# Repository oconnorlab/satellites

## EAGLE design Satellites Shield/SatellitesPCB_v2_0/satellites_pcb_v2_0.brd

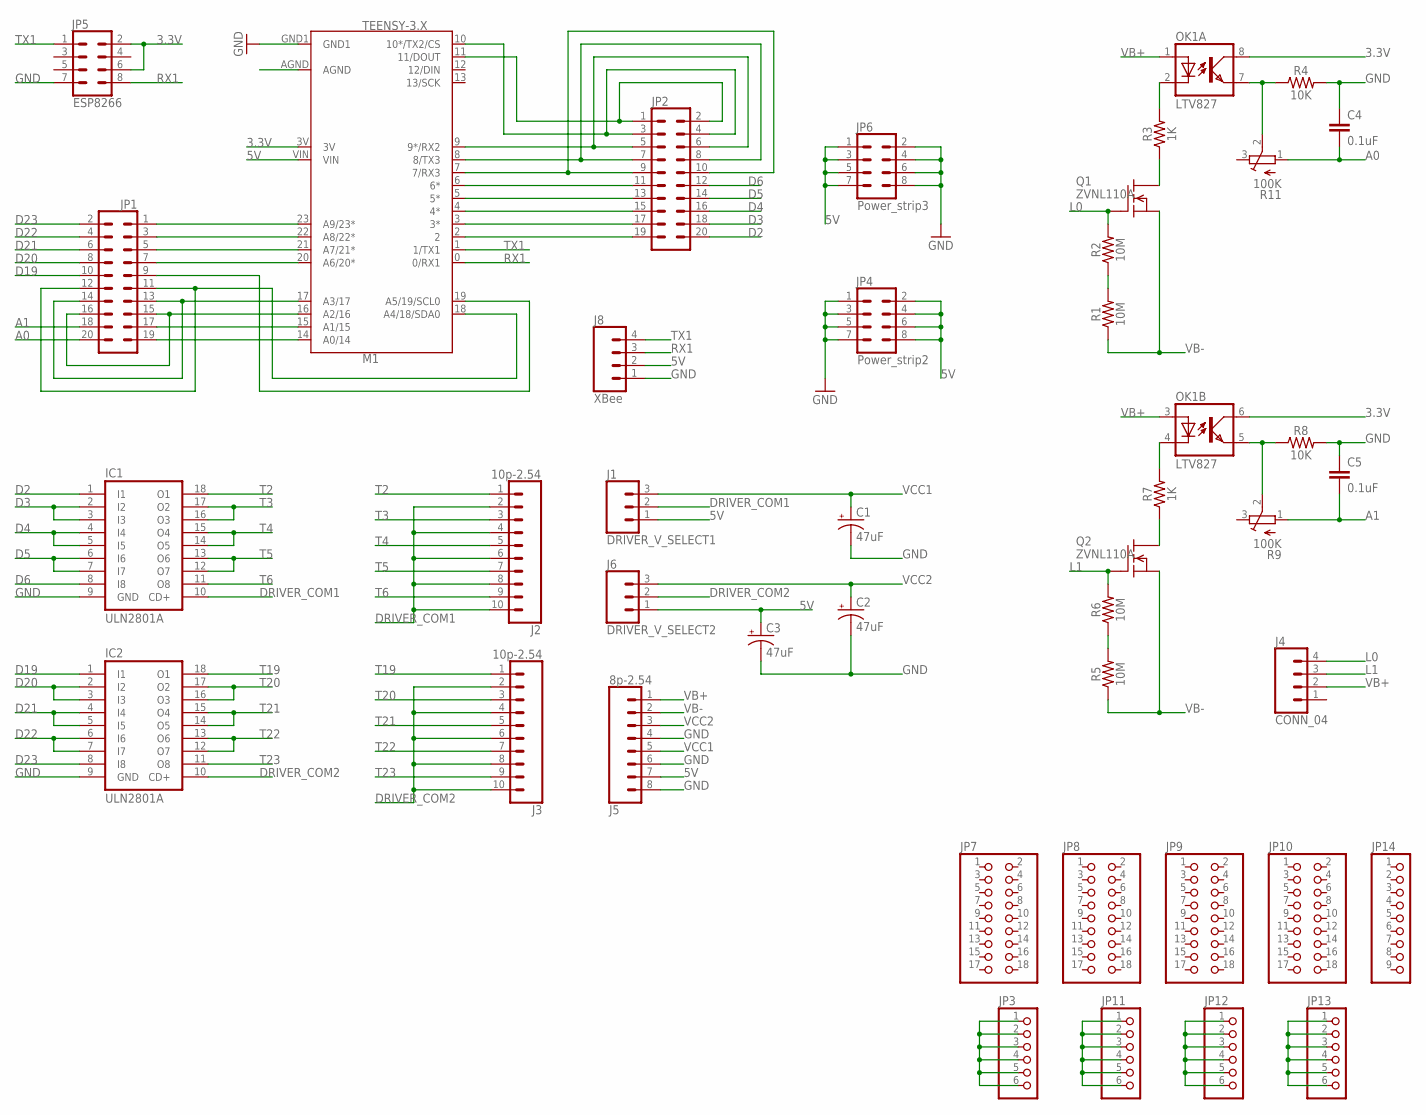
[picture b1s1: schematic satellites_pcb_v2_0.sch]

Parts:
C1, C2, C3: 47uF; CPOL-RADIAL-2.5MM-6.5MM
C4, C5: 0.1uF; CAP-PTH-2.54
IC1, IC2: ULN2801A; DIL18
J1: DRIVER_V_SELECT1; 1X03_LOCK
J2, J3: 10p-2.54; SCREW_TERMINAL_10P_2.54MM_LONGPAD
J4: CONN_04; SCREW_TERMINAL_4P_2.54MM
J5: 8p-2.54; SCREW_TERMINAL_8P_2.54MM_LONGPAD
J6: DRIVER_V_SELECT2; 1X03_LOCK
J8: XBee; 1X04_LOCK
JP1, JP2: CONN_10X2; 2X10
JP3, JP11, JP12, JP13: PINHD-1X6CLEAN; 1X06-CLEAN
JP4: Power_strip2; 2X4
JP5: ESP8266; 2X4
JP6: Power_strip3; 2X4
JP7, JP8, JP9, JP10: PINHD-2X9-CBIG; 2X09-CLEANBIG
JP14: PINHD-1X9; 1X09-BIG
M1: TEENSY-3.X; TEENSY-3.1_NOSILK
OK1: LTV827; DIP08
Q1, Q2: ZVNL110A; TO92
R1, R2, R5, R6: 10M; AXIAL-0.3
R3, R7: 1K; AXIAL-0.3
R4, R8: 10K; AXIAL-0.3
R9, R11: 100K; TRIM-3386H

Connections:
3.3V: JP5.2, JP5.6, M1.3V, OK1.6 (COL), OK1.8 (COL)
5V: C3.1 (+), J1.1, J5.7, J6.1, J8.2, JP4.2, JP4.4, JP4.6, JP4.8, JP6.1, JP6.3, JP6.5, JP6.7, M1.VIN
A0: C4.2, JP1.20, R11.1 (A)
A1: C5.2, JP1.18, R9.1 (A)
D2: IC1.1 (I1), JP2.20
D3: IC1.2 (I2), IC1.3 (I3), JP2.18
D4: IC1.4 (I4), IC1.5 (I5), JP2.16
D5: IC1.6 (I6), IC1.7 (I7), JP2.14
D6: IC1.8 (I8), JP2.12
D19: IC2.1 (I1), JP1.10
D20: IC2.2 (I2), IC2.3 (I3), JP1.8
D21: IC2.4 (I4), IC2.5 (I5), JP1.6
D22: IC2.6 (I6), IC2.7 (I7), JP1.4
D23: IC2.8 (I8), JP1.2
DRIVER_COM1: IC1.10 (CD+), J1.2, J2.2, J2.4, J2.6, J2.8, J2.10
DRIVER_COM2: IC2.10 (CD+), J3.2, J3.4, J3.6, J3.8, J3.10, J6.2
GND: C1.2 (-), C2.2 (-), C3.2 (-), C4.1, C5.1, IC1.9 (GND), IC2.9 (GND), J5.4, J5.6, J5.8, J8.1, JP4.1, JP4.3, JP4.5, JP4.7, JP5.7, JP6.2, JP6.4, JP6.6, JP6.8, M1.GND1, R4.P$2 (2), R8.P$2 (2)
L0: J4.4, Q1.2 (G), R2.P$2 (2)
L1: J4.3, Q2.2 (G), R6.P$2 (2)
unnamed: JP1.1, M1.23 (A9/23*)
unnamed: JP1.3, M1.22 (A8/22*)
unnamed: JP2.5, JP2.6, M1.9 (9*/RX2)
unnamed: JP2.7, JP2.8, M1.8 (8/TX3)
unnamed: OK1.7 (EMIT), R4.P$1 (1), R11.2 (S)
unnamed: JP2.11, M1.6 (6*)
unnamed: JP2.13, M1.5 (5*)
unnamed: JP2.3, JP2.4, M1.10 (10*/TX2/CS)
unnamed: JP2.15, M1.4 (4*)
unnamed: JP1.5, M1.21 (A7/21*)
unnamed: JP1.7, M1.20 (A6/20*)
unnamed: OK1.5 (EMIT), R8.P$1 (1), R9.2 (S)
unnamed: Q1.1 (D), R3.P$1 (1)
unnamed: JP2.17, M1.3 (3*)
unnamed: R1.P$2 (2), R2.P$1 (1)
unnamed: JP2.19, M1.2
unnamed: JP1.15, JP1.16, M1.16 (A2/16)
unnamed: JP1.17, M1.15 (A1/15)
unnamed: JP1.19, M1.14 (A0/14)
unnamed: JP1.11, JP1.12, M1.18 (A4/18/SDA0)
unnamed: JP1.9, M1.19 (A5/19/SCL0)
unnamed: OK1.2 (C), R3.P$2 (2)
unnamed: R5.P$2 (2), R6.P$1 (1)
unnamed: Q2.1 (D), R7.P$1 (1)
unnamed: OK1.4 (C), R7.P$2 (2)
unnamed: JP3.1, JP3.2, JP3.3, JP3.4, JP3.5, JP3.6
unnamed: JP11.1, JP11.2, JP11.3, JP11.4, JP11.5, JP11.6
unnamed: JP12.1, JP12.2, JP12.3, JP12.4, JP12.5, JP12.6
unnamed: JP2.9, JP2.10, M1.7 (7/RX3)
unnamed: JP13.1, JP13.2, JP13.3, JP13.4, JP13.5, JP13.6
unnamed: JP1.13, JP1.14, M1.17 (A3/17)
unnamed: JP2.1, JP2.2, M1.11 (11/DOUT)
RX1: J8.3, JP5.8, M1.0 (0/RX1)
T2: IC1.18 (O1), J2.1
T3: IC1.16 (O3), IC1.17 (O2), J2.3
T4: IC1.14 (O5), IC1.15 (O4), J2.5
T5: IC1.12 (O7), IC1.13 (O6), J2.7
T6: IC1.11 (O8), J2.9
T19: IC2.18 (O1), J3.1
T20: IC2.16 (O3), IC2.17 (O2), J3.3
T21: IC2.14 (O5), IC2.15 (O4), J3.5
T22: IC2.12 (O7), IC2.13 (O6), J3.7
T23: IC2.11 (O8), J3.9
TX1: J8.4, JP5.1, M1.1 (1/TX1)
VB+: J4.2, J5.1, OK1.1 (A), OK1.3 (A)
VB-: J5.2, Q1.3 (S), Q2.3 (S), R1.P$1 (1), R5.P$1 (1)
VCC1: C1.1 (+), J1.3, J5.5
VCC2: C2.1 (+), J5.3, J6.3

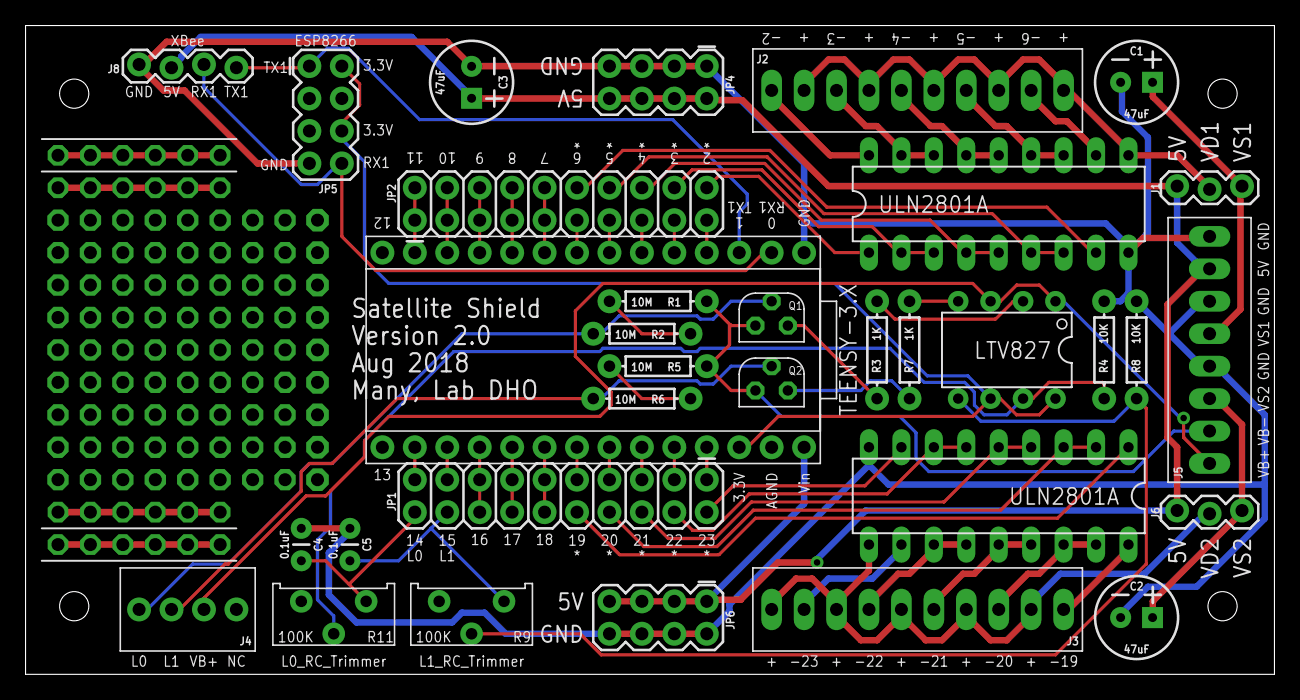
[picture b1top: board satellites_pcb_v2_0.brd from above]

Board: 2 copper layers, 97.8 x 50.8 mm, 42 parts (0 on the bottom side), 67 nets.

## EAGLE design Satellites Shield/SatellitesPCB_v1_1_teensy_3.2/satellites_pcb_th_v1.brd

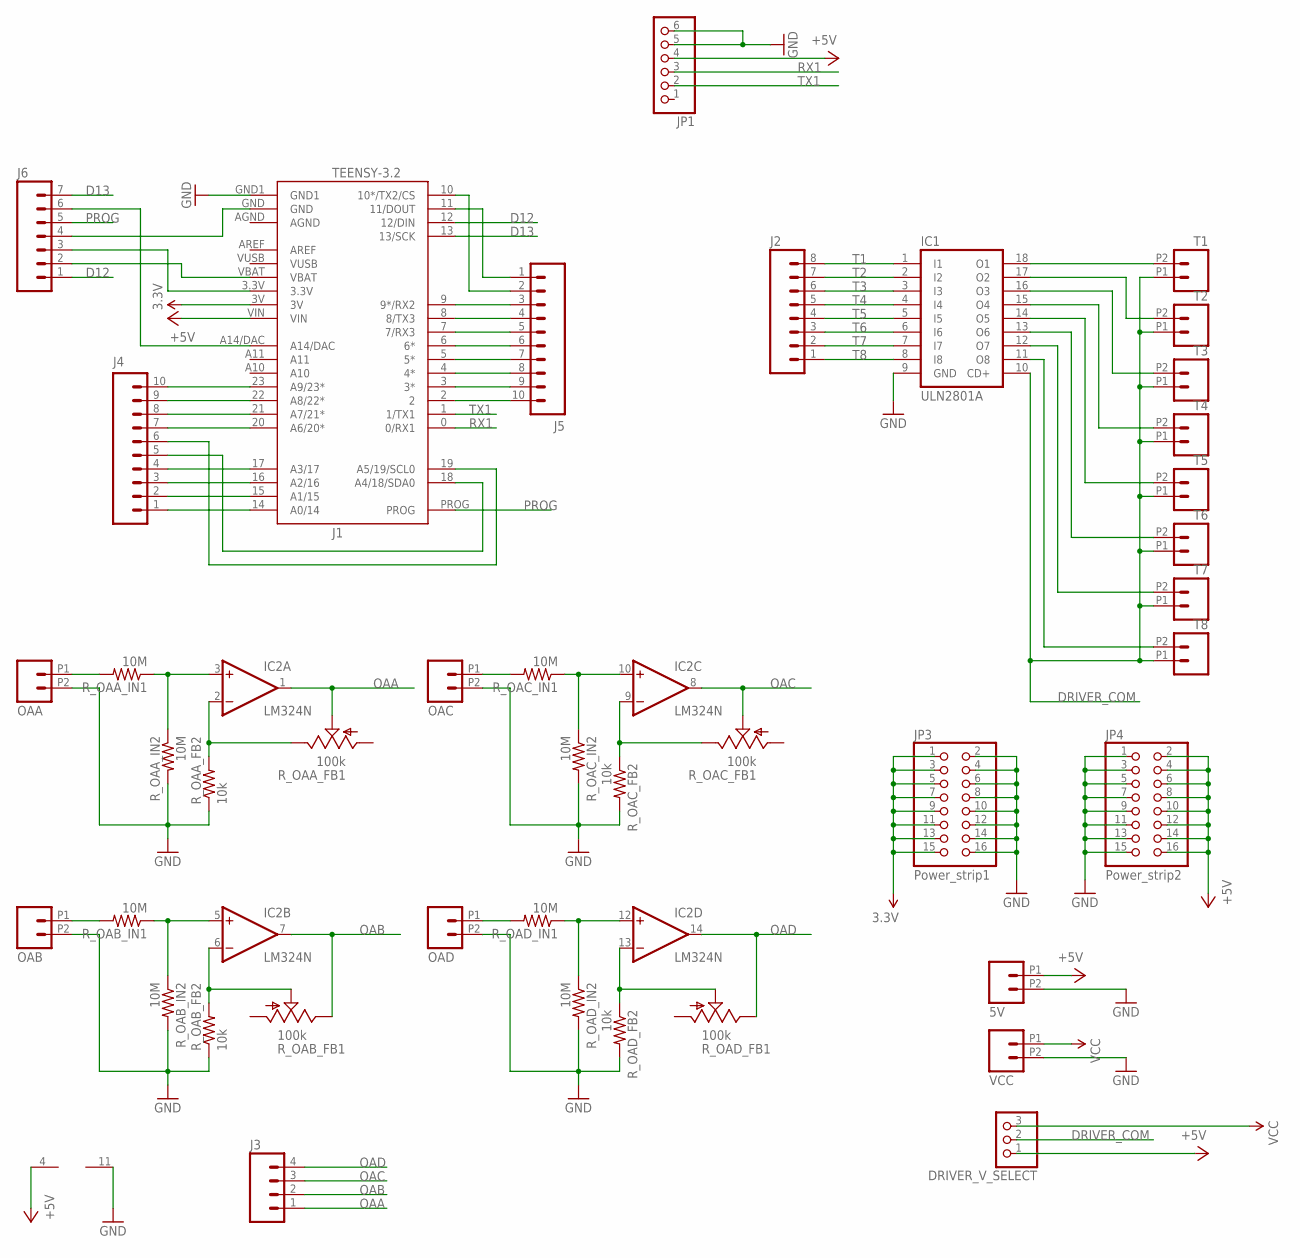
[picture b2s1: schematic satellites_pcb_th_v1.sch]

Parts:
5V: M022.54MM_SCREWTERM; 1X02_2.54_SCREWTERM
DRIVER_V_SELECT: PINHD-1X3; 1X03
IC1: ULN2801A; DIL18
IC2: LM324N; DIL14
J1: TEENSY-3.2; TEENSY-3.1_NOSILK
J2: M08; 1X08_ROUND
J3: M04PTH; 1X04
J4, J5: M10NO_SILK_PTH_FEMALE; 1X10_NO_SILK
J6: M07; 1X07
JP1: PINHD-1X6; 1X06
JP3: Power_strip1; 2X08
JP4: Power_strip2; 2X08
OAA: M022.54MM_SCREWTERM; 1X02_2.54_SCREWTERM
OAB: M022.54MM_SCREWTERM; 1X02_2.54_SCREWTERM
OAC: M022.54MM_SCREWTERM; 1X02_2.54_SCREWTERM
OAD: M022.54MM_SCREWTERM; 1X02_2.54_SCREWTERM
R_OAA_FB1: 100k; B64W
R_OAA_FB2: 10k; AXIAL-0.3
R_OAA_IN1, R_OAA_IN2: 10M; AXIAL-0.3
R_OAB_FB1: 100k; B64W
R_OAB_FB2: 10k; AXIAL-0.3
R_OAB_IN1, R_OAB_IN2: 10M; AXIAL-0.3
R_OAC_FB1: 100k; B64W
R_OAC_FB2: 10k; AXIAL-0.3
R_OAC_IN1, R_OAC_IN2: 10M; AXIAL-0.3
R_OAD_FB1: 100k; B64W
R_OAD_FB2: 10k; AXIAL-0.3
R_OAD_IN1, R_OAD_IN2: 10M; AXIAL-0.3
T1, T2, T3, T4, T5, T6, T7, T8: M022.54MM_SCREWTERM; 1X02_2.54_SCREWTERM
VCC: M022.54MM_SCREWTERM; 1X02_2.54_SCREWTERM

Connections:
3.3V: J1.3V, JP3.1, JP3.3, JP3.5, JP3.7, JP3.9, JP3.11, JP3.13, JP3.15
+5V: 5V.P1 (1), DRIVER_V_SELECT.1, IC2.4 (V+), J1.VIN, JP1.4, JP4.2, JP4.4, JP4.6, JP4.8, JP4.10, JP4.12, JP4.14, JP4.16
D12: J1.12 (12/DIN), J6.1
D13: J1.13 (13/SCK), J6.7
DRIVER_COM: DRIVER_V_SELECT.2, IC1.10 (CD+), T1.P1 (1), T2.P1 (1), T3.P1 (1), T4.P1 (1), T5.P1 (1), T6.P1 (1), T7.P1 (1), T8.P1 (1)
GND: 5V.P2 (2), IC1.9 (GND), IC2.11 (V-), J1.GND1, JP1.5, JP1.6, JP3.2, JP3.4, JP3.6, JP3.8, JP3.10, JP3.12, JP3.14, JP3.16, JP4.1, JP4.3, JP4.5, JP4.7, JP4.9, JP4.11, JP4.13, JP4.15, OAA.P2 (2), OAB.P2 (2), OAC.P2 (2), OAD.P2 (2), R_OAA_FB2.P$1 (1), R_OAA_IN2.P$2 (2), R_OAB_FB2.P$1 (1), R_OAB_IN2.P$2 (2), R_OAC_FB2.P$2 (2), R_OAC_IN2.P$2 (2), R_OAD_FB2.P$2 (2), R_OAD_IN2.P$2 (2), VCC.P2 (2)
unnamed: J1.14 (A0/14), J4.1
unnamed: J1.23 (A9/23*), J4.10
unnamed: J1.9 (9*/RX2), J5.3
unnamed: J1.8 (8/TX3), J5.4
unnamed: J1.7 (7/RX3), J5.5
unnamed: J1.6 (6*), J5.6
unnamed: J1.5 (5*), J5.7
unnamed: J1.10 (10*/TX2/CS), J5.2
unnamed: OAB.P1 (1), R_OAB_IN1.P$2 (2)
unnamed: J1.22 (A8/22*), J4.9
unnamed: J1.21 (A7/21*), J4.8
unnamed: J1.20 (A6/20*), J4.7
unnamed: IC2.3 (+IN), R_OAA_IN1.P$1 (1), R_OAA_IN2.P$1 (1)
unnamed: OAC.P1 (1), R_OAC_IN1.P$2 (2)
unnamed: IC2.10 (+IN), R_OAC_IN1.P$1 (1), R_OAC_IN2.P$1 (1)
unnamed: OAD.P1 (1), R_OAD_IN1.P$2 (2)
unnamed: J1.17 (A3/17), J4.4
unnamed: J1.16 (A2/16), J4.3
unnamed: J1.15 (A1/15), J4.2
unnamed: J1.18 (A4/18/SDA0), J4.5
unnamed: J1.19 (A5/19/SCL0), J4.6
unnamed: IC1.11 (O8), T8.P2 (2)
unnamed: J1.4 (4*), J5.8
unnamed: J1.3 (3*), J5.9
unnamed: IC1.18 (O1), T1.P2 (2)
unnamed: IC1.17 (O2), T2.P2 (2)
unnamed: IC1.16 (O3), T3.P2 (2)
unnamed: IC1.15 (O4), T4.P2 (2)
unnamed: IC1.14 (O5), T5.P2 (2)
unnamed: IC1.13 (O6), T6.P2 (2)
unnamed: IC1.12 (O7), T7.P2 (2)
unnamed: J1.2, J5.10
unnamed: J1.11 (11/DOUT), J5.1
unnamed: J1.VBAT, J6.2
unnamed: J1.A14/DAC, J6.6
unnamed: IC2.2 (-IN), R_OAA_FB1.E, R_OAA_FB2.P$2 (2)
unnamed: IC2.6 (-IN), R_OAB_FB1.S, R_OAB_FB2.P$2 (2)
unnamed: IC2.9 (-IN), R_OAC_FB1.E, R_OAC_FB2.P$1 (1)
unnamed: J1.3.3V, J6.3
unnamed: IC2.13 (-IN), R_OAD_FB1.S, R_OAD_FB2.P$1 (1)
unnamed: J1.GND, J6.4
unnamed: OAA.P1 (1), R_OAA_IN1.P$2 (2)
unnamed: IC2.5 (+IN), R_OAB_IN1.P$1 (1), R_OAB_IN2.P$1 (1)
unnamed: IC2.12 (+IN), R_OAD_IN1.P$1 (1), R_OAD_IN2.P$1 (1)
OAA: IC2.1 (OUT), J3.1, R_OAA_FB1.S
OAB: IC2.7 (OUT), J3.2, R_OAB_FB1.E
OAC: IC2.8 (OUT), J3.3, R_OAC_FB1.S
OAD: IC2.14 (OUT), J3.4, R_OAD_FB1.E
PROG: J1.PROG, J6.5
RX1: J1.0 (0/RX1), JP1.3
T1: IC1.1 (I1), J2.8
T2: IC1.2 (I2), J2.7
T3: IC1.3 (I3), J2.6
T4: IC1.4 (I4), J2.5
T5: IC1.5 (I5), J2.4
T6: IC1.6 (I6), J2.3
T7: IC1.7 (I7), J2.2
T8: IC1.8 (I8), J2.1
TX1: J1.1 (1/TX1), JP1.2
VCC: DRIVER_V_SELECT.3, VCC.P1 (1)

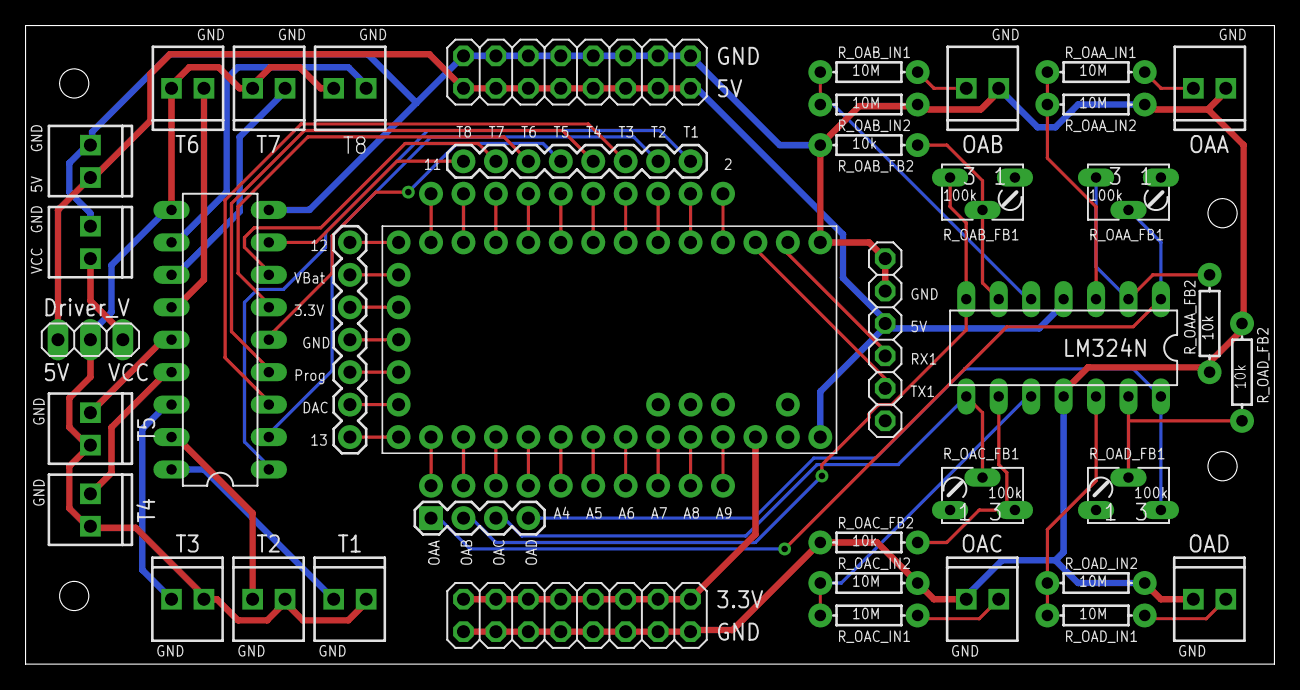
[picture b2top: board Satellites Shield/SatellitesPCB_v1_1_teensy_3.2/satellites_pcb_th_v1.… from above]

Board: 2 copper layers, 97.8 x 50.0 mm, 42 parts (0 on the bottom side), 66 nets.

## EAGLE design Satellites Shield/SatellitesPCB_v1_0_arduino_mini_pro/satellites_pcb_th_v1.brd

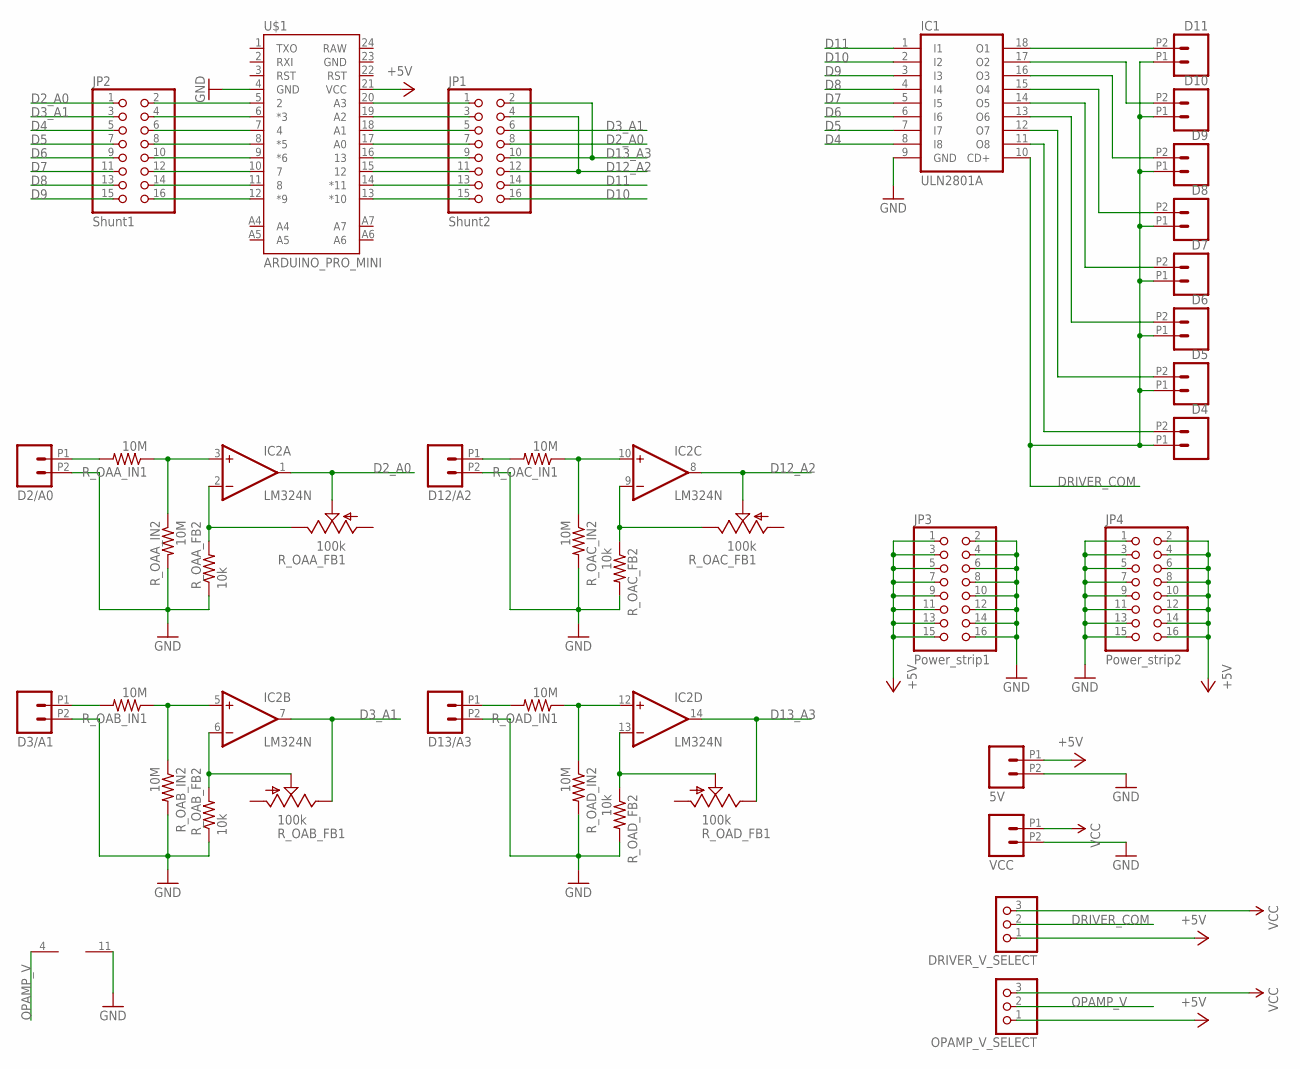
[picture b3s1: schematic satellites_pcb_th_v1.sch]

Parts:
5V: M022.54MM_SCREWTERM; 1X02_2.54_SCREWTERM
D2/A0, D3/A1, D4, D5, D6, D7, D8, D9, D10, D11, D12/A2, D13/A3: M022.54MM_SCREWTERM; 1X02_2.54_SCREWTERM
DRIVER_V_SELECT: PINHD-1X3; 1X03
IC1: ULN2801A; DIL18
IC2: LM324N; DIL14
JP1: Shunt2; 2X08
JP2: Shunt1; 2X08
JP3: Power_strip1; 2X08
JP4: Power_strip2; 2X08
OPAMP_V_SELECT: PINHD-1X3; 1X03
R_OAA_FB1: 100k; B64W
R_OAA_FB2: 10k; AXIAL-0.3
R_OAA_IN1, R_OAA_IN2: 10M; AXIAL-0.3
R_OAB_FB1: 100k; B64W
R_OAB_FB2: 10k; AXIAL-0.3
R_OAB_IN1, R_OAB_IN2: 10M; AXIAL-0.3
R_OAC_FB1: 100k; B64W
R_OAC_FB2: 10k; AXIAL-0.3
R_OAC_IN1, R_OAC_IN2: 10M; AXIAL-0.3
R_OAD_FB1: 100k; B64W
R_OAD_FB2: 10k; AXIAL-0.3
R_OAD_IN1, R_OAD_IN2: 10M; AXIAL-0.3
U$1: ARDUINO_PRO_MINI
VCC: M022.54MM_SCREWTERM; 1X02_2.54_SCREWTERM

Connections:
+5V: 5V.P1 (1), DRIVER_V_SELECT.1, JP3.1, JP3.3, JP3.5, JP3.7, JP3.9, JP3.11, JP3.13, JP3.15, JP4.2, JP4.4, JP4.6, JP4.8, JP4.10, JP4.12, JP4.14, JP4.16, OPAMP_V_SELECT.1, U$1.21 (VCC)
D2_A0: IC2.1 (OUT), JP1.8, JP2.1, R_OAA_FB1.S
D3_A1: IC2.7 (OUT), JP1.6, JP2.3, R_OAB_FB1.E
D4: IC1.8 (I8), JP2.5
D5: IC1.7 (I7), JP2.7
D6: IC1.6 (I6), JP2.9
D7: IC1.5 (I5), JP2.11
D8: IC1.4 (I4), JP2.13
D9: IC1.3 (I3), JP2.15
D10: IC1.2 (I2), JP1.16
D11: IC1.1 (I1), JP1.14
D12_A2: IC2.8 (OUT), JP1.4, JP1.12, R_OAC_FB1.S
D13_A3: IC2.14 (OUT), JP1.2, JP1.10, R_OAD_FB1.E
DRIVER_COM: D4.P1 (1), D5.P1 (1), D6.P1 (1), D7.P1 (1), D8.P1 (1), D9.P1 (1), D10.P1 (1), D11.P1 (1), DRIVER_V_SELECT.2, IC1.10 (CD+)
GND: 5V.P2 (2), D2/A0.P2 (2), D3/A1.P2 (2), D12/A2.P2 (2), D13/A3.P2 (2), IC1.9 (GND), IC2.11 (V-), JP3.2, JP3.4, JP3.6, JP3.8, JP3.10, JP3.12, JP3.14, JP3.16, JP4.1, JP4.3, JP4.5, JP4.7, JP4.9, JP4.11, JP4.13, JP4.15, R_OAA_FB2.P$1 (1), R_OAA_IN2.P$2 (2), R_OAB_FB2.P$1 (1), R_OAB_IN2.P$2 (2), R_OAC_FB2.P$2 (2), R_OAC_IN2.P$2 (2), R_OAD_FB2.P$2 (2), R_OAD_IN2.P$2 (2), U$1.4 (GND), VCC.P2 (2)
unnamed: JP2.2, U$1.5 (2)
unnamed: JP2.4, U$1.6 (*3)
unnamed: JP2.6, U$1.7 (4)
unnamed: JP2.8, U$1.8 (*5)
unnamed: JP2.10, U$1.9 (*6)
unnamed: JP2.12, U$1.10 (7)
unnamed: JP2.14, U$1.11 (8)
unnamed: JP2.16, U$1.12 (*9)
unnamed: D3/A1.P1 (1), R_OAB_IN1.P$2 (2)
unnamed: JP1.1, U$1.20 (A3)
unnamed: JP1.3, U$1.19 (A2)
unnamed: JP1.5, U$1.18 (A1)
unnamed: IC2.3 (+IN), R_OAA_IN1.P$1 (1), R_OAA_IN2.P$1 (1)
unnamed: D12/A2.P1 (1), R_OAC_IN1.P$2 (2)
unnamed: IC2.10 (+IN), R_OAC_IN1.P$1 (1), R_OAC_IN2.P$1 (1)
unnamed: D13/A3.P1 (1), R_OAD_IN1.P$2 (2)
unnamed: JP1.7, U$1.17 (A0)
unnamed: JP1.9, U$1.16 (13)
unnamed: JP1.11, U$1.15 (12)
unnamed: JP1.13, U$1.14 (*11)
unnamed: JP1.15, U$1.13 (*10)
unnamed: D4.P2 (2), IC1.11 (O8)
unnamed: D11.P2 (2), IC1.18 (O1)
unnamed: D10.P2 (2), IC1.17 (O2)
unnamed: D9.P2 (2), IC1.16 (O3)
unnamed: D8.P2 (2), IC1.15 (O4)
unnamed: D7.P2 (2), IC1.14 (O5)
unnamed: D6.P2 (2), IC1.13 (O6)
unnamed: D5.P2 (2), IC1.12 (O7)
unnamed: IC2.2 (-IN), R_OAA_FB1.E, R_OAA_FB2.P$2 (2)
unnamed: IC2.6 (-IN), R_OAB_FB1.S, R_OAB_FB2.P$2 (2)
unnamed: IC2.9 (-IN), R_OAC_FB1.E, R_OAC_FB2.P$1 (1)
unnamed: IC2.13 (-IN), R_OAD_FB1.S, R_OAD_FB2.P$1 (1)
unnamed: D2/A0.P1 (1), R_OAA_IN1.P$2 (2)
unnamed: IC2.5 (+IN), R_OAB_IN1.P$1 (1), R_OAB_IN2.P$1 (1)
unnamed: IC2.12 (+IN), R_OAD_IN1.P$1 (1), R_OAD_IN2.P$1 (1)
OPAMP_V: IC2.4 (V+), OPAMP_V_SELECT.2
VCC: DRIVER_V_SELECT.3, OPAMP_V_SELECT.3, VCC.P1 (1)

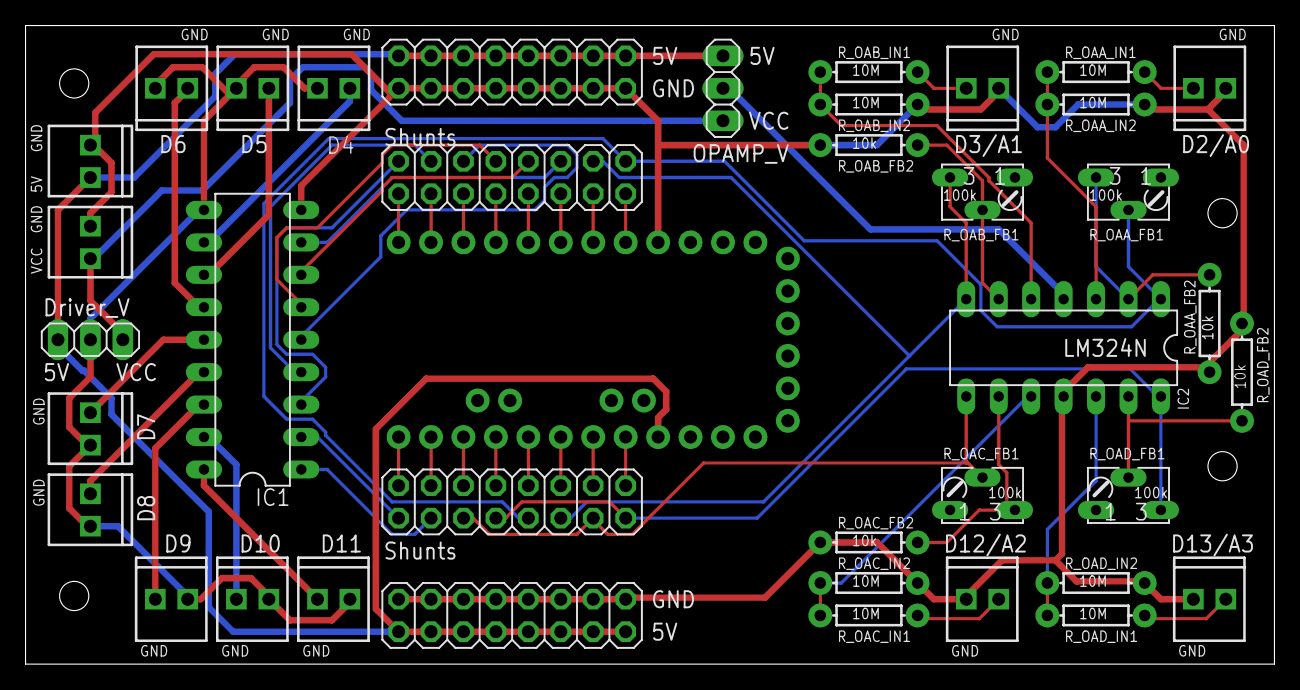
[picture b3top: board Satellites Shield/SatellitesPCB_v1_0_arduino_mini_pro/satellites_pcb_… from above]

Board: 2 copper layers, 97.8 x 50.0 mm, 39 parts (0 on the bottom side), 53 nets.

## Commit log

2018-05-11 Add Arduino libraries
    relocating from lab1 repo
2018-05-11 Load command groups as tabs
    also updated user functions
2018-07-12 Misc updates
2018-08-20 Add PCB design files
2018-08-20 Add support of boards without usb_serial_class
    Improve clarity of examples
2018-08-20 Fix outputing commands from unser function
    Previously, sent commands were not cleared.
2018-08-23 Minor bug fixes
    Remove unnecessary lines;
    Change the absence of user function from 'none' to empty string '';
    Update app installer.
2019-01-27 ZaberMotor: add streamArc2 method
    streamArc2 moves the stage in an half circle that arcs toward the negative direction of the first axis.
2019-03-01 Revamp many data importing functions
2019-03-17 Update libraries
    Move Position class from ManyRig.h to ZaberMotor.h
    ZaberMotor
    Speficy serial port at object construction
    Store Stream object as a reference instead of a pointer
    Remove the unnecessary #include "Satellites.h"
    ManyRig
2019-04-11 Update a variable name
2020-01-15 Allow users to define maxPos
2020-10-07 Add mechanical and PCB designs to repo
2020-10-15 Update examples and installer
2021-02-01 Update ManyRig
    Adding variables, etc. for auxilliary lick detection (via perch sigal)
2021-02-04 Update ManyRig
    Fixed small typo, uncommented AudioAux variables
2021-03-31 Mics modifications
2021-04-07 Minor fix ManyRig.cpp and ManyRig.h WO
    Update perch lick detector pin assignment
2021-04-07 Update ManyRig.cpp WO
    Remove AUXperchHpin AUXperchVpin
2021-04-17 SV: settings saved more UI info
    Save the locations and sizes of main window and log window on the screen.
    Save the status of "File name" text box and "Append time" checkbox.
2021-04-18 SV: settings now save command group positions
    Save the locations of opened command group windows, and apply when the windows or settings are loaded.
    Move the log window status and position variables to config struct.
2021-04-18 SV: fix that position is only applied for the first cmd group
2021-08-20 SV: fix the initialization of cmdGroupWins
    Default initialization of cmdGroupWins is [], which caused error when saving settings. Now it is {}.
    Also modified examples.
2021-09-10 SV: update installer
2022-09-02 Better handle output messages

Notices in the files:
parts and their libraries:
SparkFun-Resistors: Licensing: Creative Commons ShareAlike 4.0 International - https://creativecommons.org/licenses/by-sa/4.0
